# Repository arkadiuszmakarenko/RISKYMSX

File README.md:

# RISKYMSX

The RISKYMSX cartridge by Arkadiusz Makarenko is a compact MSX flash ROM cartridge based on the inexpensive CH32V30xVCT6 RISC-V MCU which can be easily programmed from a MSX computer using a FAT formatted USB pen drive containing ROM files.

## Main Features

* Support for up to 256KB ROMs
* SCC emulation
* Nextor 3.0 USB disk support for MSX-DOS programs and files
* Firmware programming with a WCH-LinkE; an experimental custom bootloader can update firmware from a USB stick
* ROM Flashing:
  * No external flash programmer is needed
  * A ROM can be flashed in-system using a MSX computer and a FAT-formatted USB pen drive
  * `ROM Flashing Mode` is activated by pressing GRAPH key during MSX boot
  * Automatic flashing of ROMs from USB can be achieved via specially named ROM archives
  * Manually flashing of ROMs from USB is done using a simple interactive menu
  * Automatic mapper type detection from the ROM content when flashing manually (same heuristic as openMSX)
  * FAT long filenames are supported
* Supported mappers:
  * Standard 16KB ROMs
  * Standard 32KB ROMs
  * Standard 48KB /64KB ROMs
  * KONAMI without SCC
  * KONAMI with SCC (EN - SCC emulation enabled)
  * KONAMI with SCC (DIS - SCC emulation disabled)
  * ASCII 8K
  * ASCII 16K
  * Neo 8k
  * Neo 16k

## Hardware

The RISKYMSX cartridge is made up of a 4-layer PCB with a reduced set of SMD components and through-hole connectors:
* A WCH [CH32V303VCT6](https://www.wch-ic.com/products/CH32V303.html) MCU (or alternatively a [CH32V307VCT6](https://www.wch-ic.com/products/CH32V307.html))
* Two LEDs, one to indicate power on state, and one lit during `ROM Flashing Mode`
* On rev 2.2, a CH217K current-limited switch controls power to the USB host port
* A [LM1117](https://www.ti.com/lit/ds/symlink/lm1117.pdf) voltage regulator to provide +3V3 to the MCU from the +5V rail of the MSX cartridge slot
* A [MCP6001](https://ww1.microchip.com/downloads/aemDocuments/documents/MSLD/ProductDocuments/DataSheets/MCP6001-1R-1U-2-4-1-MHz-Low-Power-Op-Amp-DS20001733L.pdf) operational amplifier to enhance the SCC audio signal fed into the MSX cartridge SOUNDIN pin
* Three headers:
  * B0: open for normal operation; closed to select system boot, including the optional custom bootloader
  * DAT/CLK: unconnected by default, used to program the MCU using the [`WCH-LinkE`](https://www.wch-ic.com/products/WCH-Link.html) programmer via SWDIO/SWCLK
  * RX/TX: unconnected by default, serial debug console
* One USB Type-A female connector
* Several passives required for proper operation of the above components

### Revisions

There are several hardware revisions of the cartridge. The main ones are listed here in reverse chronological order.

#### Rev 2.2 (current)

Rev 2.2 adds a CH217K switch to the USB host port. Its active-low enable is
controlled by PB12 and its fault output is connected to PB13. The USB port is
intended to power a USB drive, not to power the cartridge from a PC. Use
firmware that supports this switch.

The [schematic and PCB](board/), [rev 2.2 Gerbers](board/gerbers/RISKYMSXv22.zip),
and [schematic BOM](RISKYMSXCart.csv) are in this repository. The BOM requires
verification before ordering or assembly.

#### Rev 2.1 (older)

This version introduces the following changes:
* the flash button is removed, as the flashing interface can be accessed by pressing the GRAPH key on the MSX keyboard during boot
* unnecessary leds are removed, leaving just the Flash and Power leds
* the audio amplifier circuit is enhanced with a low pass filter 

#### Rev 2 (obsolete)

This version introduces the following changes:
* the LM1117 voltage regulator and related passives are moved to the back of the PCB
* the B1 header is removed as it has no practical use
* a simple audio amplifier circuit is added for SCC sound

|
|-|-|
|RISKYMSX Rev 2 front render|RISKYMSX Rev 2 rear render|

#### Rev 1 (obsolete)

This is the initial revision of the RISKYMSX cartridge.

|
|-|-|
|RISKYMSX Rev 1 front render|RISKYMSX Rev 1 rear render|

## Firmware

The firmware implements two different modes of operation for the RISKYMSX cartridge:
* `Normal Mode`. In this mode a ROM cartridge is emulated according to the last ROM flashed using the `ROM Flashing Mode`.
* `ROM Flashing Mode`. In this mode a ROM can be flashed manually or automatically into the cartridge by using a FAT formatted USB pen drive.

### Automated releases

GitHub Actions builds the bootloader, firmware, and Nextor cartridge on pushes
and pull requests to `main`. Pushing a version tag matching
`firmware/User/version.h` (currently `v4.2.1`) automatically creates a GitHub
Release containing:

* Firmware `.bin` and `.hex` files, plus the `CART.NXT` Nextor cartridge image
* `Bootloader.bin`, the experimental custom bootloader image (not application firmware)
* A ZIP of the PCB Gerber and drill files
* `SHA256SUMS` checksums for the release files

Successful pushes to `main` also update the `latest-build` prerelease with
the same assets and the commit SHA, if the built commit is still the tip of
`main`. Its tag and assets are replaced on each update; older rolling builds
are not retained. If the current build fails, the previous release remains.
Versioned releases remain separate, and pull requests do not publish releases.

The BOM is not included in new release packages. Previously published releases
may contain an outdated BOM. Verify the current schematic BOM before ordering
parts.

Create and push a tag to publish a release:

```bash
git tag v4.2.1
git push origin v4.2.1
```

## Building a RISKYMSX cartridge

You will need good soldering skills and specific equipment to build a RISKYMSX cartridge.
As you probably saw on the Bill Of Materials, there are quite small SMD components like 0603 passives and a LQFP-100 package with 0.5mm pitch that need to be soldered.

> [!WARNING]
> If you are building new boards, please use the current available board revision.

### PCB

The PCB can be fabricated from the [rev 2.2 Gerber archive](board/gerbers/RISKYMSXv22.zip).
The [rev 2.1 archive](RiskyMSXv21PCB.zip) is retained for older boards.

### Suggested tools

These are example tools used during the manual building of the RISKYMSX cartridge:

* silicone heat-resistant mat (TE-616 400x290mm), to avoid burning your precious desk
* electronic microscope with 2 LEDs (KKmoon 3" LCD 10X-300X 3.0MP 1080P HDMI electronic digital video microscope), to be able to solder those small 0.5mm pitch pins
* temperature controlled soldering station (Yihua 908D), to make good soldering joints
* T-1C "horseshoe", T-I and T-1.6D soldering tips (900M series), use the best fitting one for each soldering job
* copper sponge, for soldering head cleaning
* flux (Mechanic UV80 flux paste), to help keep components in place and achieve good soldering joints
* solder (0.5mm, for hobby projects you may use 60% Sn / 40% Pb Flux 2% at your own risk)
* desoldering wick (2.5mm is fine), for correcting mistakes if you are human)

### Components and assembly

The [CSV BOM](RISKYMSXCart.csv) is generated from the current schematic, but
is not a verified shopping list or assembly guide. Check component values,
ratings, footprints, orientation, and population before ordering or assembly.
U2 is `CH32V303VCT6`; the schematic retains the existing CH32V307 library
symbol, so verify its pin assignments against the CH32V303 datasheet.
The [interactive BOM](board/bom/ibom.html) shows the current PCB and its
component positions. It is also not a verified shopping list.

To regenerate the CSV with KiCad 10 from the repository root:

```sh
kicad-cli sch export bom \
  --fields 'Reference,Value,Footprint,QUANTITY,DNP' \
  --labels 'Reference,Value,Footprint,Qty,DNP' \
  --group-by 'Value,Footprint,DNP' --ref-range-delimiter '' \
  -o RISKYMSXCart.csv board/RISKYMSXCart.kicad_sch
```

The `DNP` column records KiCad's do-not-populate status. The list includes the
MSX edge connector footprint, which is part of the PCB rather than a separate
component. KiCad's PCB DRC reports footprint-library warnings; review those
before fabrication.

To regenerate the interactive BOM, install the KiCad 10-compatible
[InteractiveHtmlBom](https://github.com/openscopeproject/InteractiveHtmlBom)
plugin and run it from PCB Editor, or use its command-line tool:

```sh
generate_interactive_bom --no-browser --dest-dir bom board/RISKYMSXCart.kicad_pcb
```

The interactive BOM is generated from PCB values; synchronize the PCB with the
schematic and check for mismatches before regenerating it.

### Building the firmware on Linux

> [!NOTE]
> These instructions have been validated using Ubuntu 24.04.2 LTS.

#### Cloning the RISKYMSX github repository

```bash
cd $HOME
git clone 'https://github.com/arkadiuszmakarenko/RISKYMSX.git'
```

This will clone the RISKYMSX github repository to the `RISKYMSX` directory under your home directory.

#### Installing the [MounRiverStudio IDE](http://www.mounriver.com)

1. Download the MounRiverStudio package for Linux

[http://www.mounriver.com/download](http://www.mounriver.com/download)

Choose the package in `tar.xz` format.

2. Uncompress the MounRiverStudio package into a known directory

For example this will uncompress the MounRiverStudio package into the IDE directory under your home directory.

```bash
export IDEDIR=$HOME/IDE
mkdir -p $IDEDIR && cd $IDEDIR
tar xJvf /path/to/MounRiverStudio_Linux_X64_V210.tar.xz
```

Once uncompressed, all package files are under the `MRS2` directory.

3. Setup the MounRiverStudio

You can follow the instructions described on the `README` file.
Alternatively, if you don't want to install library files system-wide you can follow these instructions:

* Change to the `MRS2/beforeinstall` directory

```bash
cd MRS2/beforeinstall
```

* Make a backup of the `start.sh` script file for reference

```bash
cp start.sh start.sh.orig
```

* Modify the `start.sh` script file.

Comment out the lines that install libraries and the line that gives world write access to all files under the `MRS-linux-x64` directory.
Leave as is the code that copies the udev rules for the WCH programmers and reloads them into udevadm.

```bash
#! /bin/bash
#echo  -e "\nCopy Libs"
#sudo cp -P ./lib*    /usr/lib
#echo  -e "Register new Libs"
#sudo ldconfig
echo "copy rules"
sudo cp ./50-wch.rules /etc/udev/rules.d
sudo cp ./60-openocd.rules  /etc/udev/rules.d
echo "Reload rules"
sudo udevadm control  --reload-rules

#chmod -R 777 ../MRS-linux-x64
chmod -R 750 ../MRS-linux-x64

echo -e "DONE"
```

* Run the modified `start.sh` script

```bash
chmod u+x start.sh
./start.sh
```

* Make the `chrome-sandbox` executable suid to root by changing the ownership of the file to root and setting the SUID bit.

This is required as the MounRiverStudio IDE is an Electron-based application that uses a sandbox approach.

```bash
cd ../MRS-linux-x64
sudo chown root chrome-sandbox
sudo chmod 4755 chrome-sandbox
```

#### Launching the MounRiverStudio IDE

If you installed the MounRiverStudio IDE under `$HOME/IDE`, use the following complete command line whenever you need to launch MounRiverStudio IDE specifying where to find the extra libraries needed.

```bash
cd $HOME/IDE/MRS2/MRS-linux-x64
LD_LIBRARY_PATH=$(readlink -f ../beforeinstall/) ./mounriver-studio\ 2
```

#### Generating the firmware file

1. After launching the MounRiverStudio IDE, open the RISKYMSXCART project file

`File | Open MounRiver Project`

**`/path/to/your/RISKYMSX/firmware/RISKYMSXCART.wvproj`**

The project file is under the `firmware` directory on the cloned github repository.

2. Build the project

`Project | Build Project`

#### Generating the firmware file from the command line

As an alternative to the MounRiverStudio IDE, the firmware can be built and flashed directly from the command line using GNU `make`.

Requirements:

* GNU `make`
* A RISC-V toolchain. The Makefile auto-detects, in order:
  1. A locally installed `MRS_Toolchain_Linux_x64_V210/RISC-V Embedded GCC12` at the repository root (not shipped in the repo)
  2. `riscv-wch-elf-gcc` on `PATH` (the same compiler MounRiver uses)
  3. `riscv-none-embed-gcc` on `PATH` (xPack)
  4. `riscv64-unknown-elf-gcc` on `PATH` (system package)
* For `make flash`: OpenOCD with WCH-Link support (the Makefile uses the WCH version from the local MounRiver toolchain when available)
* For rebuilding `CART.NXT`: the .NET runtime needed by the vendored N80 assembler

The default build also attempts to build Nextor and copy it to `build/CART.NXT`.
It prints a warning rather than failing if the Nextor build fails; check the
output and do not assume an existing `CART.NXT` is fresh.

#### Building all images from the repository root

Run `make` from the repository root to build the bootloader, firmware, and
Nextor cartridge. The output files are placed in the root:
`Bootloader.bin`, `RISKYMSXCART.bin`, `RISKYMSXCART.hex`, and `CART.NXT`.
Individual builds are available with `make bootloader`, `make firmware`, or
`make nextor`; `make clean` removes the local firmware and bootloader outputs
and build directories. It leaves the tracked `CART.NXT` release image in place.

Build the firmware:

```bash
cd firmware
make            # produces build/RISKYMSXCART.{elf,bin,hex,map}
make size       # show program/data sizes
make clean      # remove build artifacts
```

Build and program the chip with OpenOCD and a WCH-LinkE:

```bash
make flash
```

You can override the toolchain explicitly, for example to force a clean build with the xPack toolchain:

```bash
make TOOLCHAIN_DIR=/opt/xpack PREFIX=riscv-none-embed- clean all
```

#### Programming the firmware

Firmware programming changes the MCU application, whereas ROM flashing in the
cartridge menu only selects an MSX ROM. Use a WCH-LinkE for initial programming
and recovery. The optional custom bootloader offers a different, experimental
way to update the application from an MSX and USB stick after installation.

> [!WARNING]
> On rev 2.2 the CH217K switches the USB host VBUS. A USB cable connected to
> a PC is not a suitable source of cartridge power. The old USB ISP
> cable-only instructions do not apply to this revision. USB ISP with an
> independently powered board has not been validated here.
>
> Use a properly powered target and a common ground with the WCH-Link. A
> specific standalone power connection for rev 2.2 has not yet been
> validated; consult the schematic and verify the supply, voltage and
> connections before programming. Do not bypass the switch or connect
> multiple power sources based on the old instructions.

##### Programming the application with WCH-LinkE

1. With power off, connect WCH-LinkE SWCLK/TCK to J8 CLK, SWDIO/TMS to
   J8 DAT, and the programmer ground to target ground. Follow the
   [WCH-Link manual](https://www.wch-ic.com/downloads/WCH-LinkUserManual_PDF.html)
   for the programmer's target-voltage requirements and RISC-V mode.
2. Provide the target with a verified supply, connect the WCH-LinkE to the PC
   and confirm the cartridge is powered. The target power arrangement must be
   verified for the board revision; it is not supplied by the USB host port.
3. Use `make flash` in `firmware/`, or select the built
   `firmware/obj/RISKYMSXCART.hex` in MounRiverStudio under
   `Flash | Download Configuration` and use `Flash | Download`. The
   command-line build produces `firmware/build/RISKYMSXCART.hex` instead.
4. Verify the operation with the programmer. Power down before disconnecting
   wires or inserting or removing the cartridge. Keep B0 open for normal boot.

##### Updating with the custom bootloader (experimental)

The [custom bootloader](bootloader/README.md) is not the CH32V303 factory ISP
bootloader. It occupies the 28 KiB system boot flash and must first be
installed using a WCH-Link and a compatible `minichlink`; it is not installed
by programming the normal application firmware.

> [!CAUTION]
> Replacing the factory bootloader is untested and hardware-dependent. It
> removes factory USB/USART ISP while installed, and a failed write or unusable
> backup can prevent recovery. Back up the system boot region first, keep the
> WCH-Link available, and read the complete
> [installation and recovery instructions](bootloader/README.md) before
> proceeding. Flash programming and MSX bus timing need hardware validation.

After the custom bootloader has been installed and validated:

1. Copy the application binary to the root of a FAT-formatted USB stick as
   `RISKYMSXCART.BIN`. The bootloader also checks `FIRMWARE.BIN` and
   `UPDATE.BIN`, in that order. Release binaries with a version in their name
   must be renamed.
2. With the MSX powered off, close B0, insert the cartridge and USB stick, and
   power on the MSX. B0 selects system boot; the cartridge is powered by the
   MSX, not by the USB stick.
3. Follow the MSX screen: press Return to program or Esc to cancel. Wait for
   programming and read-back verification to finish.
4. Power off the MSX, open B0, then power on again to run the application.
   Never remove or insert the cartridge while the MSX is powered on.

## Cartridge Operation

The RISKYMSX cartridge can operate in two different modes once programmed with the RISKYMSX firmware.

Make sure the MSX computer is powered off before inserting or removing the RISKYMSX cartridge or any other cartridge.

> [!WARNING]
> Leave DAT/CLK and RX/TX unconnected for ordinary cartridge operation. B0
> must be open for normal boot; closing it selects system boot for the
> optional custom bootloader.

### Normal Mode

In `Normal mode` the RISKYMSX cartridge behaves as a ROM cartridge once a ROM has been flashed.

Just insert the RISKYMSX cartridge and enjoy the already flashed ROM.

### ROM Flashing Mode

In `ROM Flashing Mode` a ROM file residing in a USB drive can be flashed to the RISKYMSX cartridge for later use in `Normal Mode`.

1. Make sure the MSX computer is powered off

2. Insert the RISKYMSX cartridge

3. Press and hold the `GRAPH` key on the MSX computer keyboard and power on the MSX computer.

You can release the `GRAPH` key once you see the Flash LED turn on.

4. If no USB drive is connected to the RISKYMSX cartridge, the "Insert USB" screen will appear.

You will need to connect a FAT-formatted USB drive to continue the ROM flashing procedure.

Once that is done, the RISKYMSX will try first to auto-flash a ROM before switching to manually flashing ROMs.

#### Auto-flashing ROMs

The RISKYMSX firmware will automatically flash the first file found on the root directory of the connected FAT-formatted USB drive matching one of the special filenames for ROM auto-flashing, according to the following table. A mapper will be automatically assigned based on the filename detected.

 | Mapper               | filename         | 
 |   :-----------:      | :--------------: | 
 | 16KB ROM             | cart.r16         | 
 | 32KB ROM             | cart.r32         | 
 | 48KB / 64KB ROM      | cart.r48         |
 | KONAMI without SCC   | cart.ko4         |
 | KONAMI with SCC(EN)  | cart.ko5         |
 | KONAMI with SCC(DIS) | cart.kd5         |
 | ASCII8k              | cart.a8k         | 
 | ASCII16k             | cart.a16         | 
 | NEO16                | cart.n16         | 
 | NEO8                 | cart.n8k         | 

So for example, to automatically flash F1SPIRIT.ROM, which is a KONAMI with SCC game, the F1SPIRIT.ROM file can be copied to the root of the USB drive using the filename **cart.ko5**, and then follow the mentioned procedure.

After flashing the ROM file, the RISKYMSX will automatically reboot the MSX computer and the ROM will load.

Note that if several files matching the auto-flashing filenames are found on the USB drive, only the file that causes the first match in the above table order will be flashed.

#### Manually flashing ROMs

If the connected FAT-formatted USB drive contains no files matching the auto-flashing filenames, the RISKYMSX firmware will display the interactive ROM flashing menu.

Use the following keys to interact with the file menu screen:
* `Up`, `Down`: move up or down the red arrow cursor across the available files in the current page
* `Right`: go to the next page (if more files are available to list)
* `Left`: go to the previous page (if any pagination was done before)
* `Return`: select a file for flashing
* `Esc`: go to the previous screen, or reload the file list on the root directory
* `1`: show the current flashed ROM file and mapper type, and optionally change the mapper type
* `N`: flash `CART.NXT` from the USB root as a Nextor cartridge
* `Backspace`: go to the previous directory level on the file menu

Useful tips:
* The bottom of the file menu screen shows the keys that are available to use at any moment
* Files and directories are listed alphabetically (directories first, upper/lowercase ignored), regardless of how many files a folder contains
* You can always hot-swap the USB drive while in the file menu, and once a new USB drive is connected you need to press `Esc` to refresh the file contents
* DO NOT navigate or select files while you have disconnected a USB drive without pressing `Esc` first
* Pressing `1` and choosing `SCC only (no ROM)` stores only the mapper setting in the config area (no ROM data is flashed). The cart then emulates just the SCC (0x9000-0x98FF, triggered by CS2 rather than SLTSL) on every boot unless GRAPH is held to enter the terminal
* If you flash a ROM with the wrong mapper type, you can change the mapper type easily, without reflashing the ROM again, by pressing `1` (the mapper type detected from the flashed ROM content is pre-selected there too)

When a ROM file is selected by pressing the `Return` key the mapper selection screen shows up. The mapper type is auto-detected from the ROM content and pre-selected (shown as `Detected:`), so pressing `Return` again flashes the ROM with the detected mapper. You can still move the cursor to pick a different mapper type before pressing `Return`.

Select the correct mapper type for the selected ROM file and press `Return` to start flashing the ROM.

Once the flashing process finishes the RISKYMSX firmware will reboot the MSX computer and the flashed ROM will load.

#### Nextor USB disk

Nextor 3 turns the cartridge into a USB mass-storage disk controller for
MSX-DOS. The cartridge exposes one USB device to Nextor, which maps its
compatible partitions to MSX drives.

**Minimum for the Nextor 3 DOS environment:**

* An MSX with at least 128 KiB of mapped RAM, a RISKYMSX cartridge with the
  current firmware, and the Nextor cartridge image `CART.NXT`.
* A USB mass-storage device with 512-byte sectors, an MBR partition table
  (not GPT), and a FAT16 or FAT12 partition. FAT16 is recommended. Nextor
  does **not** support FAT32, exFAT, or NTFS.
* Stable Nextor 3.0 `NEXTOR.SYS` and `COMMAND3.COM` in the root of the
  partition used to boot.

Without 128 KiB of mapped RAM, Nextor falls back to MSX-DOS 1 mode; that
mode requires a FAT12 partition with at most three sectors per FAT and, for
the DOS prompt, at least 64 KiB of RAM plus the MSX-DOS 1 system files. See the
[Nextor user manual](https://konamiman.github.io/Nextor/Nextor_3.0_User_Manual.html)
for details.

**Enable and boot Nextor:**

1. Get `CART.NXT` from a [RISKYMSX release](https://github.com/arkadiuszmakarenko/RISKYMSX/releases)
   or run `make nextor` at the repository root.
2. Copy `CART.NXT` to the root of a FAT-formatted USB stick for flashing.
   Enter ROM flashing mode by holding `GRAPH` at startup, and press `N` in
   the file menu. This replaces the currently flashed cartridge ROM with
   Nextor; it does not replace the MCU firmware.
3. Prepare a separate Nextor USB disk as described above. Download
   [Nextor 3.0 tools.zip](https://github.com/Konamiman/Nextor/releases/tag/tools-disk-image-and-zip-for-Nextor-3.0),
   extract it, and copy `NEXTOR.SYS` and `COMMAND3.COM` to the boot
   partition's root. The `TOOLS` and `HELP` directories are optional but
   useful; copy them as well if desired.
4. Insert the Nextor disk and restart the MSX normally, without holding
   `GRAPH`. The flashed Nextor kernel loads the system files from the disk.

Nextor maps active FAT12/16 partitions at boot; if none is active, it uses the
first suitable partition. Partitioning or formatting erases data, so back up
the USB device first. For partitioning and other commands, see the
[Nextor getting started guide](https://konamiman.github.io/Nextor/Nextor_3.0_Getting_Started_Guide.html)
and [Nextor downloads](https://konamiman.github.io/Nextor/releases/). The
kernel and system files must be compatible; this build uses stable Nextor 3.0
([Nextor build](NextorDriver/Makefile)).

## General troubleshooting

* If no LEDs light at power-up, check the power rails and inspect for shorts.
* On rev 2.2, a rapidly flashing activity LED can indicate a CH217K
  over-current or over-temperature fault. The firmware disables USB power and
  latches the fault until reset. Remove the cause before resetting.
* If a ROM can be programmed but the MSX cannot load it, inspect the address,
  data and bus connections and their solder joints.

## Compatibility

The RISKYMSX cartridge has been tested on the following MSX computers:

| **Model**                | **RISKYMSX**              |
|--------------------------|---------------------------|
| Sony MSX HB-101P         |          OK               |
| Sony MSX HB-501F         |          OK               |
| Toshiba MSX HX-10        |          OK               |
| Philips MSX2 VG-8235     |          OK               |
| Panasonic MSX2+ FS-A1WSX |          OK               |
| Omega MSX2+              |          OK               |
| Tides Rider MSX2+        |          OK               |
| TFMSX Rev 1 MSX2+        |          OK               |
| TFMSX Rev 2 MSX2+        |          OK               |
| MSXVR                    |          `NOK`            |

Other MSX compatible computers will probably work too, but have not been specifically tested.

## Enclosures

### Acrylic Enclosure

You can complete your RISKYMSX cartridge with an [acrylic enclosure](https://github.com/herraa1/msx-riskymsx-enclosure) suitable for all RISKYMSX cartridge board revisions.

### 3D Printed Enclosure

Another option for closing your RISKY MSX Cartridge is following project  [Enclosure](https://github.com/rafaelan00/RISKYMSX-Enclosure)

## Acknowledgments

The following people contributed to this project and supported me with technical aspects of this project.
* Terrible Fire
* cnlohr 
* NYYRIKKI
* Aoineko
* BG Ollie
* MadHacker

Testing team:
* PhilC
* Higgy
* ahmsx
* Hee-Bong An
  
Thank you very much for your support.

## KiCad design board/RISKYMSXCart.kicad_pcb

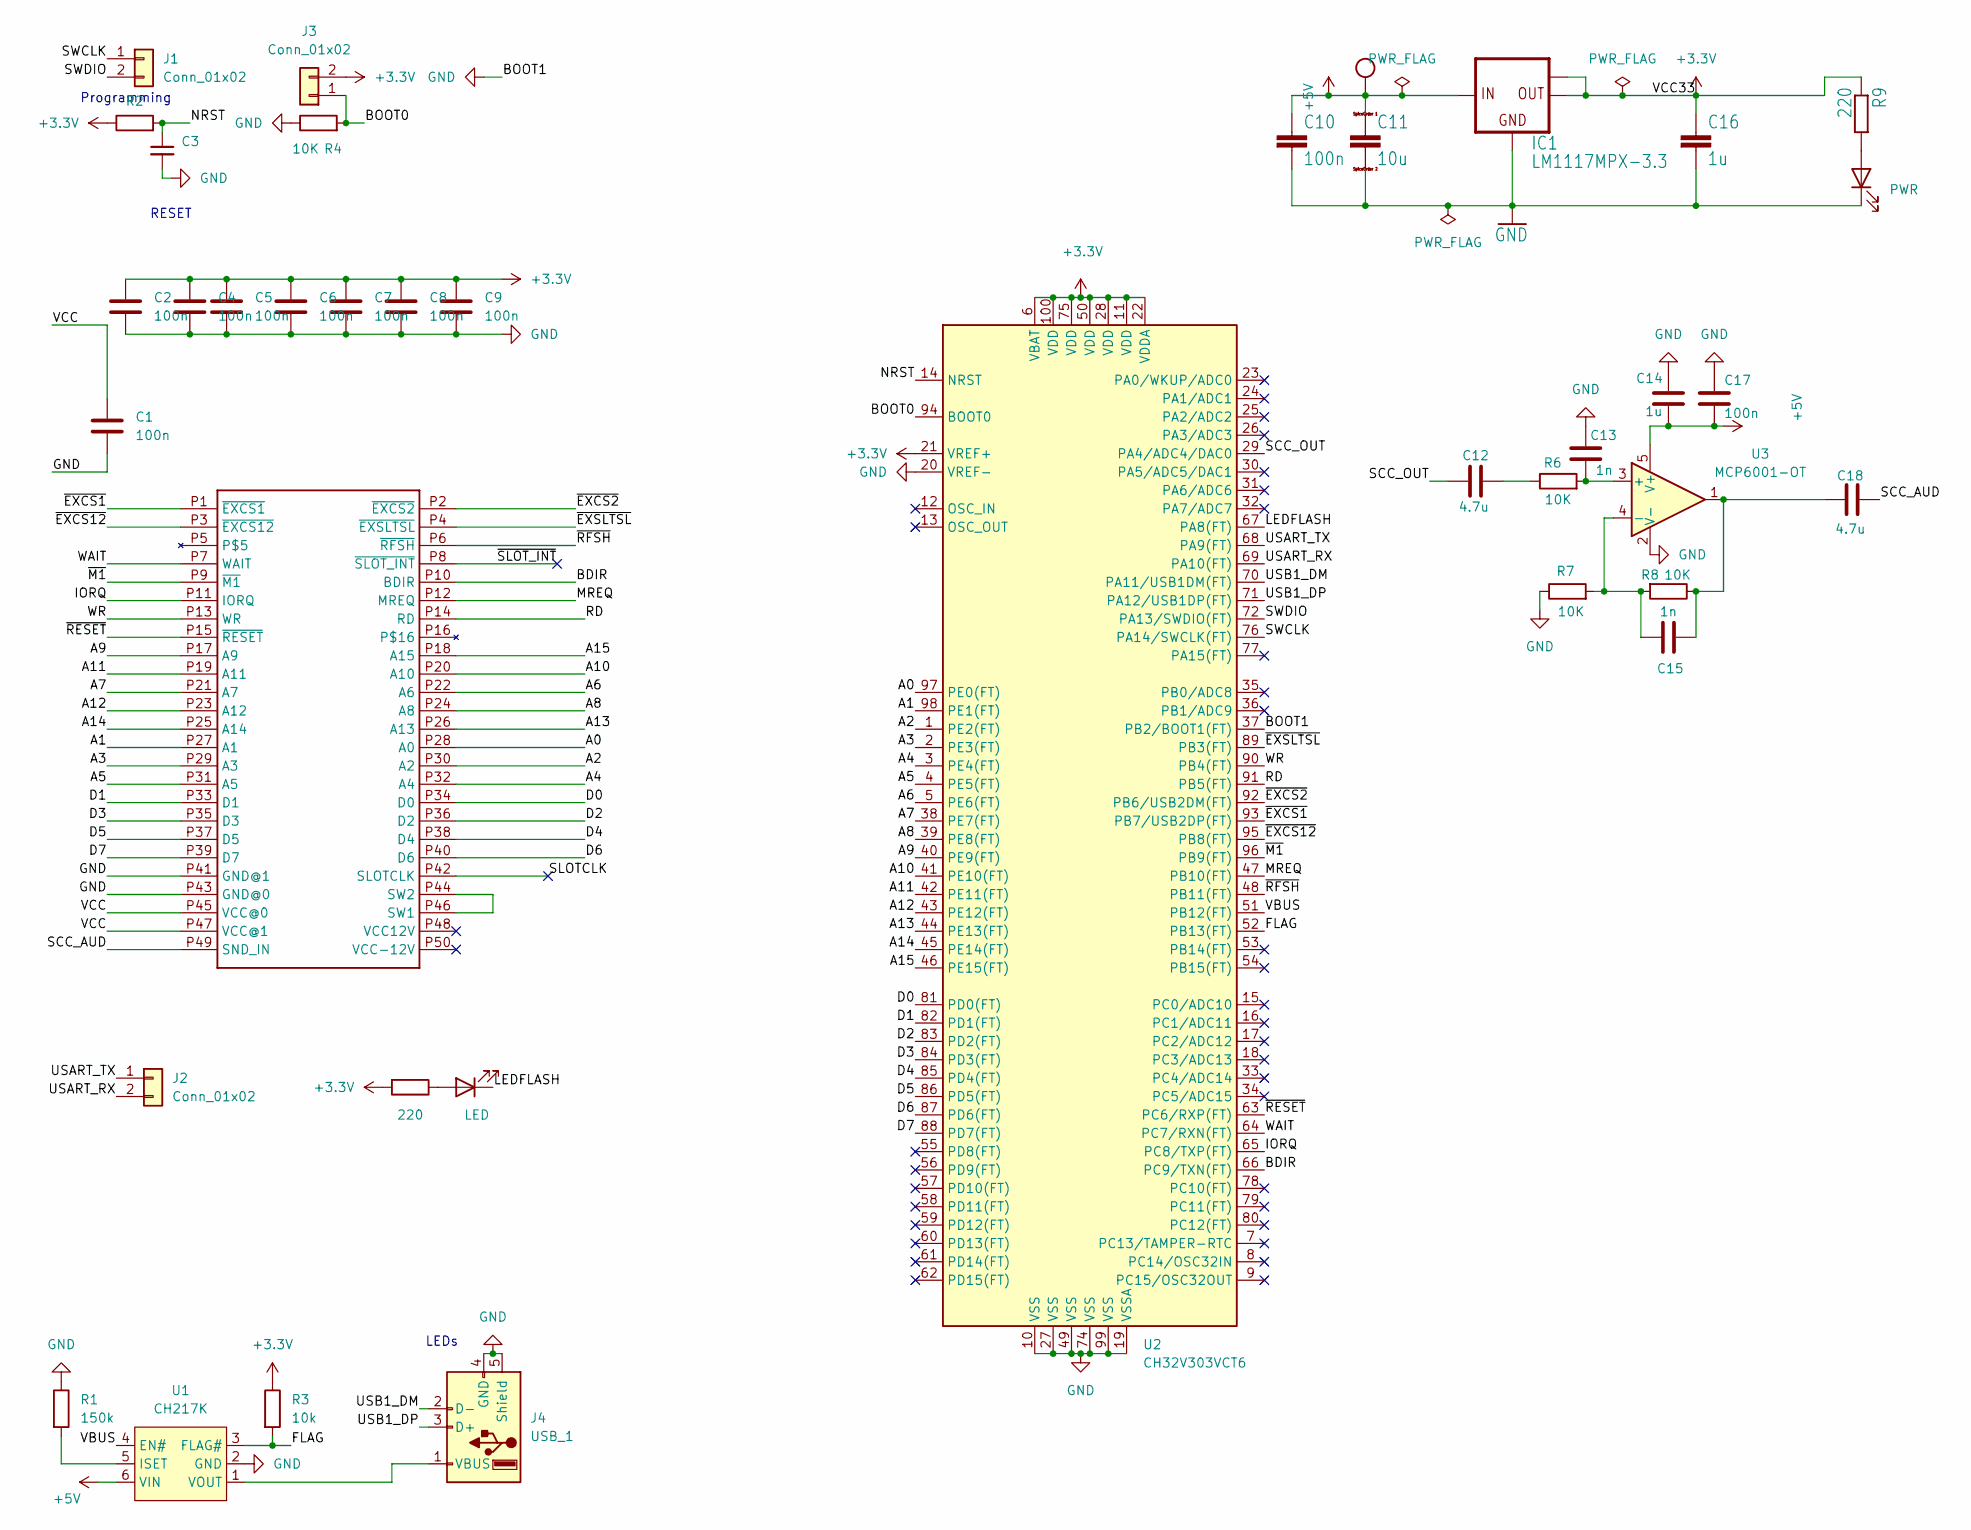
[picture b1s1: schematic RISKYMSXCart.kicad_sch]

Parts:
C1: 100n; C_1206_3216Metric_Pad1.33x1.80mm_HandSolder
C2, C4, C5, C6, C7, C8, C9, C17: 100n; C_0603_1608Metric_Pad1.08x0.95mm_HandSolder
C3: 100n; C_0603_1608Metric_Pad1.08x0.95mm_HandSolder; LCSC C14663
C10: 100n; C1206
C11: 10u; C0603
C12, C18: 4.7u; C_0603_1608Metric_Pad1.08x0.95mm_HandSolder
C13, C15: 1n; C_0603_1608Metric_Pad1.08x0.95mm_HandSolder
C14: 1u; C_0603_1608Metric_Pad1.08x0.95mm_HandSolder
C16: 1u; C1206
CN1: MSX_CART
D1: LED; LED_0805_2012Metric_Pad1.15x1.40mm_HandSolder
D2: PWR; LED_0805_2012Metric_Pad1.15x1.40mm_HandSolder
IC1: LM1117MPX-3.3; SOT223
J1, J2, J3: Conn_01x02; PinHeader_1x02_P2.54mm_Vertical
J4: USB_1; USB_A_CONNFLY_DS1095-WNR0
R1: 150k; R_0603_1608Metric_Pad0.98x0.95mm_HandSolder
R2, R4, R6, R7, R8: 10K; R_0603_1608Metric_Pad0.98x0.95mm_HandSolder
R3: 10k; R_0603_1608Metric_Pad0.98x0.95mm_HandSolder
R5: 220; R_0603_1608Metric_Pad0.98x0.95mm_HandSolder
R9: 220; R0603
U1: CH217K; SOT-23-6
U2: CH32V303VCT6; LQFP-100_14x14mm_P0.5mm
U3: MCP6001-OT; SOT-23-5

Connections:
+3.3V: C2.1, C4.1, C5.1, C6.1, C7.1, C8.1, C9.1, C16.1, IC1.2 (OUT), IC1.TAB (OUT1), J3.2, R2.1, R3.1, R5.2, R9.1, U2.6 (VBAT), U2.11 (VDD), U2.21 (VREF+), U2.22 (VDDA), U2.28 (VDD), U2.50 (VDD), U2.75 (VDD), U2.100 (VDD)
+5V: C1.1, C10.1, C11.1, C14.2, C17.2, CN1.P45 (VCC@0), CN1.P47 (VCC@1), IC1.3 (IN), U1.6 (VIN), U3.5 (V+)
/A0: CN1.P28 (A0), U2.97 (PE0(FT))
/A1: CN1.P27 (A1), U2.98 (PE1(FT))
/A2: CN1.P30 (A2), U2.1 (PE2(FT))
/A3: CN1.P29 (A3), U2.2 (PE3(FT))
/A4: CN1.P32 (A4), U2.3 (PE4(FT))
/A5: CN1.P31 (A5), U2.4 (PE5(FT))
/A6: CN1.P22 (A6), U2.5 (PE6(FT))
/A7: CN1.P21 (A7), U2.38 (PE7(FT))
/A8: CN1.P24 (A8), U2.39 (PE8(FT))
/A9: CN1.P17 (A9), U2.40 (PE9(FT))
/A10: CN1.P20 (A10), U2.41 (PE10(FT))
/A11: CN1.P19 (A11), U2.42 (PE11(FT))
/A12: CN1.P23 (A12), U2.43 (PE12(FT))
/A13: CN1.P26 (A13), U2.44 (PE13(FT))
/A14: CN1.P25 (A14), U2.45 (PE14(FT))
/A15: CN1.P18 (A15), U2.46 (PE15(FT))
/BDIR: CN1.P10 (BDIR), U2.66 (PC9/TXN(FT))
/BOOT0: J3.1, R4.2, U2.94 (BOOT0)
/D0: CN1.P34 (D0), U2.81 (PD0(FT))
/D1: CN1.P33 (D1), U2.82 (PD1(FT))
/D2: CN1.P36 (D2), U2.83 (PD2(FT))
/D3: CN1.P35 (D3), U2.84 (PD3(FT))
/D4: CN1.P38 (D4), U2.85 (PD4(FT))
/D5: CN1.P37 (D5), U2.86 (PD5(FT))
/D6: CN1.P40 (D6), U2.87 (PD6(FT))
/D7: CN1.P39 (D7), U2.88 (PD7(FT))
/FLAG: R3.2, U1.3 (FLAG#), U2.52 (PB13(FT))
/IORQ: CN1.P11 (IORQ), U2.65 (PC8/TXP(FT))
/LEDFLASH: D1.1 (K), U2.67 (PA8(FT))
/MREQ: CN1.P12 (MREQ), U2.47 (PB10(FT))
/NRST: C3.1, R2.2, U2.14 (NRST)
/RD: CN1.P14 (RD), U2.91 (PB5(FT))
/SCC_AUD: C18.2, CN1.P49 (SND_IN)
/SCC_OUT: C12.1, U2.29 (PA4/ADC4/DAC0)
/SLOTCLK: CN1.P42 (SLOTCLK)
/SWCLK: J1.1, U2.76 (PA14/SWCLK(FT))
/SWDIO: J1.2, U2.72 (PA13/SWDIO(FT))
/USART_RX: J2.2, U2.69 (PA10(FT))
/USART_TX: J2.1, U2.68 (PA9(FT))
/USB1_DM: J4.2 (D-), U2.70 (PA11/USB1DM(FT))
/USB1_DP: J4.3 (D+), U2.71 (PA12/USB1DP(FT))
/VBUS: U1.4 (EN#), U2.51 (PB12(FT))
/WAIT: CN1.P7 (WAIT), U2.64 (PC7/RXN(FT))
/WR: CN1.P13 (WR), U2.90 (PB4(FT))
/~EXCS1: CN1.P1 (~EXCS1), U2.93 (PB7/USB2DP(FT))
/~EXCS2: CN1.P2 (~EXCS2), U2.92 (PB6/USB2DM(FT))
/~EXCS12: CN1.P3 (~EXCS12), U2.95 (PB8(FT))
/~EXSLTSL: CN1.P4 (~EXSLTSL), U2.89 (PB3(FT))
/~M1: CN1.P9 (~M1), U2.96 (PB9(FT))
/~RESET: CN1.P15 (~RESET), U2.63 (PC6/RXP(FT))
/~RFSH: CN1.P6 (~RFSH), U2.48 (PB11(FT))
/~SLOT_INT: CN1.P8 (~SLOT_INT)
GND: C1.2, C2.2, C3.2, C4.2, C5.2, C6.2, C7.2, C8.2, C9.2, C10.2, C11.2, C13.2, C14.1, C16.2, C17.1, CN1.P41 (GND@1), CN1.P43 (GND@0), D2.1 (K), IC1.1 (GND), J4.4 (GND), J4.5 (Shield), R1.1, R4.1, R7.1, U1.2 (GND), U2.10 (VSS), U2.19 (VSSA), U2.20 (VREF-), U2.27 (VSS), U2.37 (PB2/BOOT1(FT)), U2.49 (VSS), U2.74 (VSS), U2.99 (VSS), U3.2 (V-)
unnamed: C12.2, R6.1
unnamed: C15.2, C18.1, R8.1, U3.1
unnamed: CN1.P44 (SW2), CN1.P46 (SW1)
unnamed: D1.2 (A), R5.1
unnamed: D2.2 (A), R9.2
unnamed: J4.1 (VBUS), U1.1 (VOUT)
unnamed: R1.2, U1.5 (ISET)
unnamed: C13.1, R6.2, U3.3 (+)
unnamed: C15.1, R7.2, R8.2, U3.4 (-)

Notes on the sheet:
RESET
Programming
LEDs

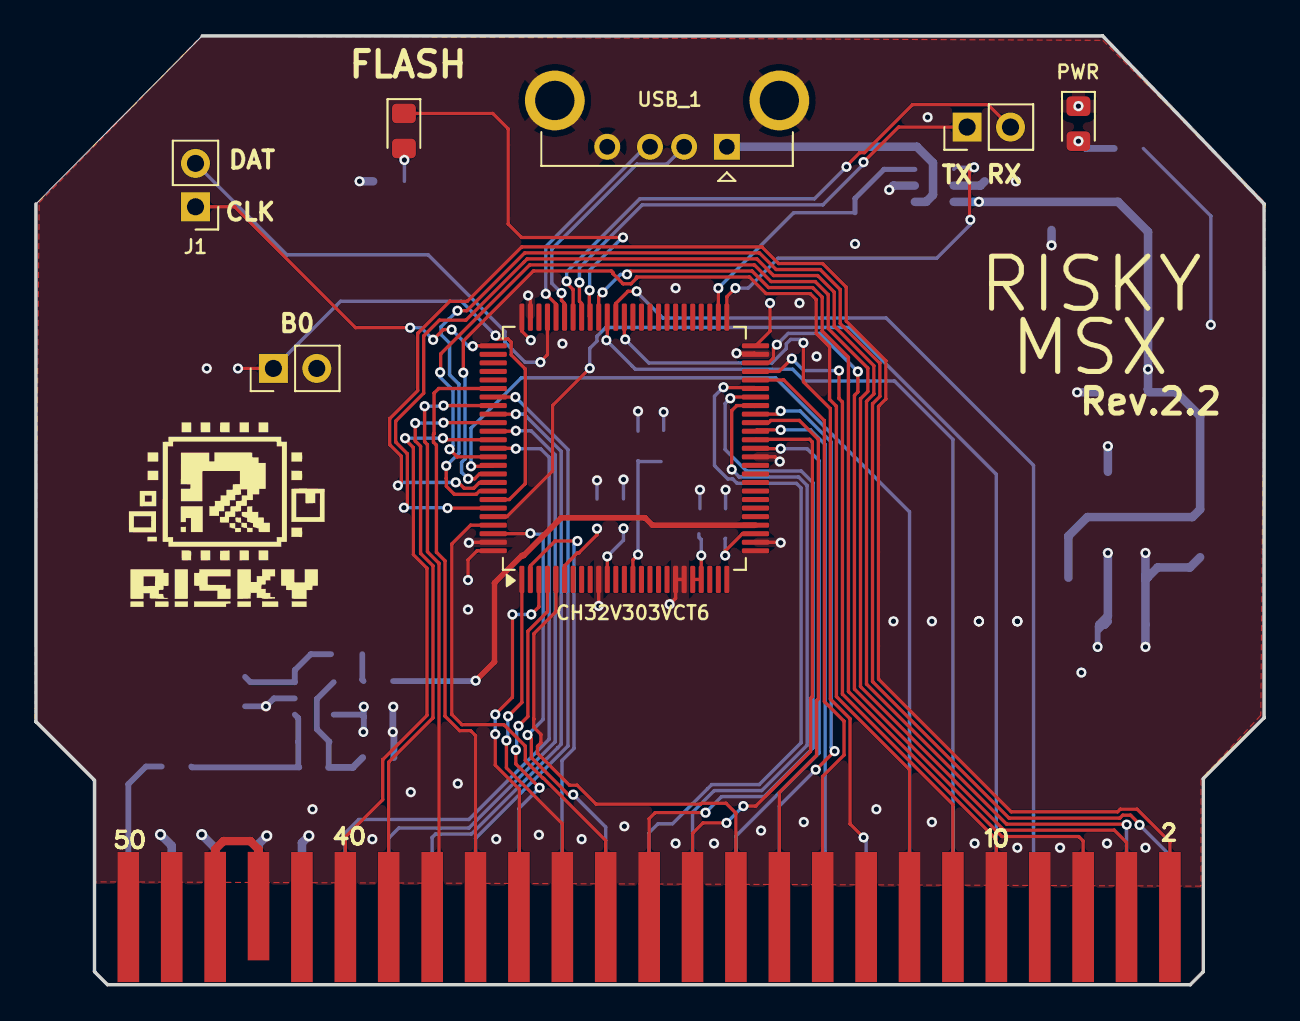
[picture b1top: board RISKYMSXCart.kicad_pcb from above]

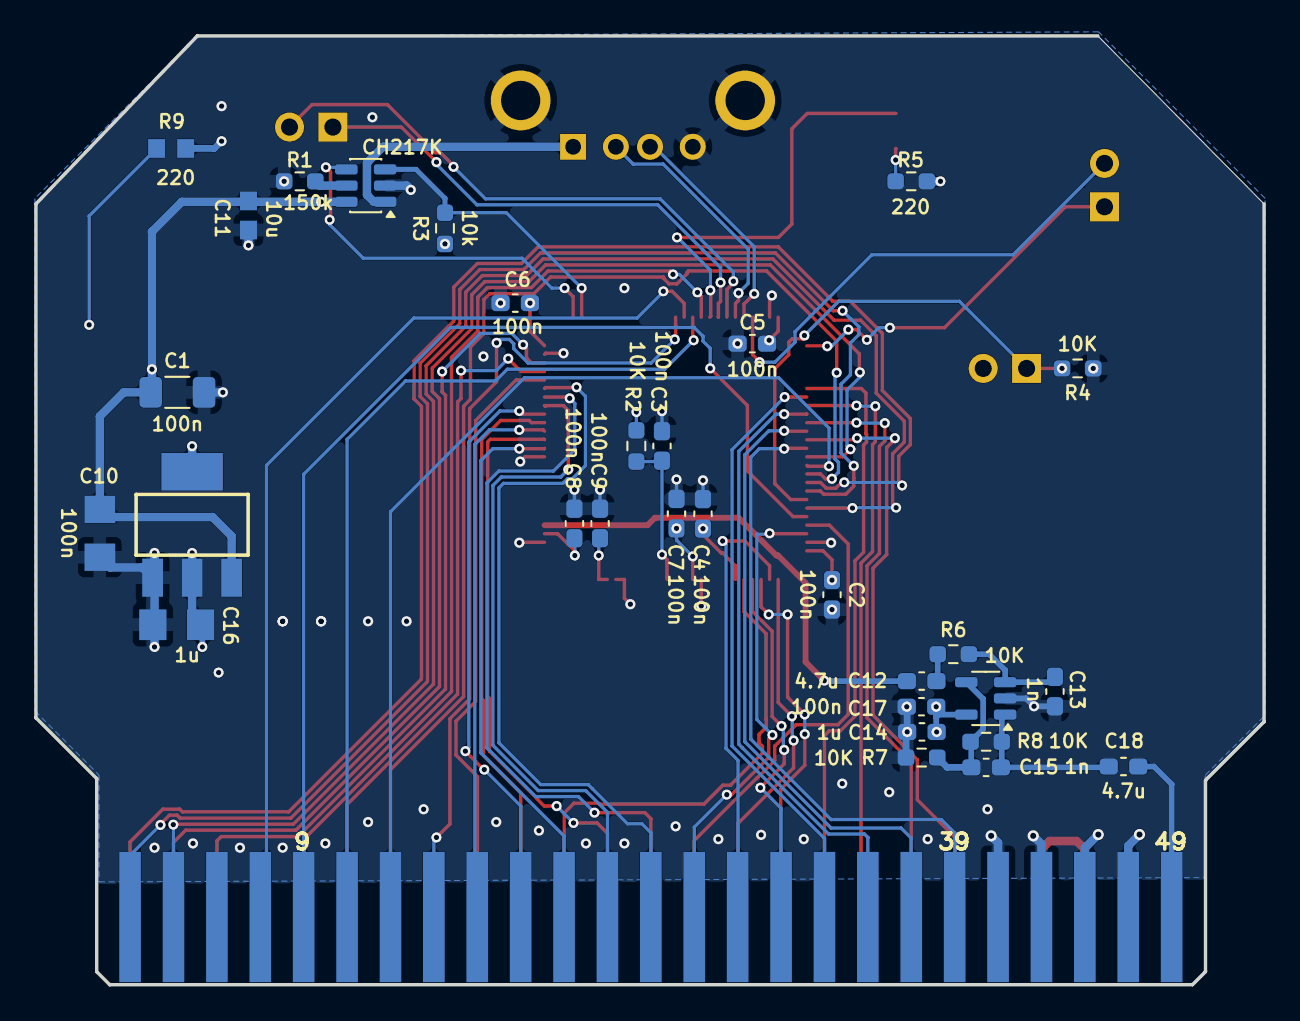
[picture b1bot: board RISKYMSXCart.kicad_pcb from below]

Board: 4 copper layers, 71.9 x 55.5 mm, 38 parts (30 on the bottom side), 62 nets.

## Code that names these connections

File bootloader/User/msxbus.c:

#include "msxbus.h"
#include "ch32v30x.h"
#include <string.h>

/*
 * MSX cartridge bus interception.
 *
 * GPIOE carries the address, GPIOD the data bus. PB3 is SLT, PB4 WR and PB5
 * RD, all active low. The MSX side program (MSXTerminal/msxterminal.asm)
 * reads a byte from #7FFF and writes a byte to #7FFD. #7FFE selects the
 * terminal (0) or the cartridge ROM (non-zero).
 */

MsxOutQueue msx_out;
MsxInQueue msx_in;
volatile uint8_t msx_terminal_requested;

/*
 * Handover flag for switching from the terminal to the cartridge ROM.
 *
 * The cartridge firmware reads this byte at startup: a non-zero value means
 * the terminal handed over to the ROM, a zero value means the terminal mode
 * was requested. The address is the same one the cartridge firmware uses, so
 * the two agree on the protocol across the reset.
 */
#define MSX_CART_RAM_FLAG ((volatile uint8_t *)0x20007C00u)

static const uint8_t msxterm[205] = {
    'A', 'B', '&', '@', 0x00, 0x00, 0x00, 0x00, 0x00, 0x00, 0x00, 0x00, 0x00, 0x00, 0x00, 0x00,
    'R', 'I', 'S', 'K', 'Y', '_', 'B', 'O', 'O', 'T', 0x00, '1', '.', '0', 0x00, 0x00, '>',
    0x04, '2', 0xfe, 0x7f, 0xc9, '!', '3', '@', 0x11, 0x00, 0xe0, 0x01, 0x92, 0x00, 0xd5, 0xed,
    0xb0, 0xc9, 0xaf, '2', 0xfe, 0x7f, '>', ' ', '2', 0xaf, 0xf3, '!', 0x0f, 0x00, '"', 0xea,
    0xf3, '"', 0xe9, 0xf3, '>', 0x01, 0xcd, '_', 0x00, '!', 0xc5, '@', 0x11, 0x00, '8', 0x01,
    0x08, 0x00, 0xcd, 0x5c, 0x00, '>', 0x08, '!', 0x03, 0x1b, 0xcd, 'M', 0x00, ':', 0xff, 0x7f,
    0xfe, 0x03, '(', '+', 0xfe, 0x04, '(', 0x14, 0xa7, 0xcc, 0x87, 0xe0, 0xc4, 0xa2, 0x00,
    0xcd, 0x9c, 0x00, '(', 0xe9, 0xcd, 0x9f, 0x00, '2', 0xfd, 0x7f, 0x18, 0xe1, ':', 0xff,
    0x7f, '!', 0x01, 0x1b, 0xcd, 'M', 0x00, ':', 0xff, 0x7f, '=', '-', 0xcd, 'M', 0x00, 0x18,
    0xce, 0xcd, 0x87, 0xe0, 0xcd, 0x87, 0xe0, '*', 0xb1, 0xf6, 0x11, 0xf4, 0xff, 0x19, 0xe5,
    '^', '#', 'V', '!', 0xa3, '}', 0xe7, 0xe1, ' ', 0x0c, 0x11, '|', 0xe0, 's', '#', 'r', 0xc9,
    0xc1, 0xe1, 0xc3, 0x84, '}', 0x1e, 'R', 0xcd, 0xb1, 0xff, 0xc7, 0xf5, 0xfb, '!', 0x9e,
    0xfc, '~', 0xbe, '(', 0xfd, 0xf1, 0xc9, ' ', '0', '8', '<', '8', '0', ' ', 0x00
};

void MsxBus_Init(void)
{
    msx_out.head = 0;
    msx_out.tail = 0;
    msx_in.head = 0;
    msx_in.tail = 0;
    msx_terminal_requested = 0;

    /* Clear the handover flag: the application firmware must not see a stale
       value from an earlier boot. */
    *MSX_CART_RAM_FLAG = 0;

    RCC->APB2PCENR |= RCC_APB2Periph_GPIOA | RCC_APB2Periph_GPIOB |
                      RCC_APB2Periph_GPIOC | RCC_APB2Periph_GPIOD |
                      RCC_APB2Periph_GPIOE | RCC_APB2Periph_AFIO;

    /* Address (GPIOE) and data (GPIOD) lines are inputs; the bus is driven
       only while a read cycle is being serviced. */
    GPIOE->CFGLR = 0x44444444;
    GPIOD->CFGLR = MSX_BUS_OFF;

    GPIO_InitTypeDef gpio;
    gpio.GPIO_Pin = GPIO_Pin_8;
    gpio.GPIO_Mode = GPIO_Mode_Out_PP;
    gpio.GPIO_Speed = GPIO_Speed_50MHz;
    GPIO_Init(GPIOA, &gpio);

    EXTI_InitTypeDef exti = {0};
    GPIO_EXTILineConfig(GPIO_PortSourceGPIOB, GPIO_PinSource3);
    exti.EXTI_Line = EXTI_Line3;
    exti.EXTI_Mode = EXTI_Mode_Interrupt;
    exti.EXTI_Trigger = EXTI_Trigger_Falling;
    exti.EXTI_LineCmd = ENABLE;
    EXTI_Init(&exti);

    NVIC_EnableIRQ(EXTI3_IRQn);
    SetVTFIRQ((uint32_t)MsxBus_Service, EXTI3_IRQn, 0, ENABLE);
}

void MsxBus_QueueByte(uint8_t value)
{
    uint8_t next = (uint8_t)((msx_out.head + 1) & (MSX_OUT_SIZE - 1));
    /* Wait for the MSX side to drain the queue instead of dropping the byte.
       A dropped byte in the middle of an escape sequence leaves the terminal
       in a broken state, and a dropped newline makes the output run together
       on one line. The cartridge firmware blocks the same way. */
    while (next == msx_out.tail) {
    }
    msx_out.data[msx_out.head] = value;
    msx_out.head = next;
}

void MsxBus_QueueString(const char *text)
{
    while (*text) {
        MsxBus_QueueByte((uint8_t)*text++);
    }
}

void MsxBus_Flush(void)
{
    while (msx_out.head != msx_out.tail) {
    }
}

int MsxBus_TakeInput(uint8_t *value)
{
    if (msx_in.head == msx_in.tail) {
        return 0;
    }
    *value = msx_in.data[msx_in.tail];
    msx_in.tail = (uint8_t)((msx_in.tail + 1) & (MSX_IN_SIZE - 1));
    return 1;
}

/*
 * The cartridge firmware checks this flag at startup: a non-zero value means
 * the terminal handed over to the ROM. The bootloader clears it on start, so
 * the application firmware does not mistake a bootloader run for a terminal
 * request.
 */
int MsxBus_RomModeRequested(void)
{
    return *MSX_CART_RAM_FLAG != 0;
}

void Vbus_Init(void)
{
    GPIO_InitTypeDef gpio;

    RCC->APB2PCENR |= RCC_APB2Periph_GPIOB;

    /* PB12 drives the CH217K EN# input: push pull output, initially high so
       the port stays unpowered until it is explicitly enabled. */
    gpio.GPIO_Pin = GPIO_Pin_12;
    gpio.GPIO_Mode = GPIO_Mode_Out_PP;
    gpio.GPIO_Speed = GPIO_Speed_50MHz;
    GPIO_Init(GPIOB, &gpio);
    GPIO_SetBits(GPIOB, GPIO_Pin_12);

    /* PB13 reads the CH217K FLAG# output: active low, open drain, held high
       by an internal pull-up when there is no fault. */
    gpio.GPIO_Pin = GPIO_Pin_13;
    gpio.GPIO_Mode = GPIO_Mode_IPU;
    gpio.GPIO_Speed = GPIO_Speed_50MHz;
    GPIO_Init(GPIOB, &gpio);
}

void Vbus_Enable(void)
{
    /* EN# is active low: drive PB12 low to power the USB host port. */
    GPIO_ResetBits(GPIOB, GPIO_Pin_12);
}

void Vbus_Disable(void)
{
    GPIO_SetBits(GPIOB, GPIO_Pin_12);
}

int Vbus_Faulted(void)
{
    /* FLAG# is active low: a low level means over-current or over-temperature. */
    return GPIO_ReadInputDataBit(GPIOB, GPIO_Pin_13) == Bit_RESET;
}

/*
 * Runs from the EXTI3 vector (SLT falling edge). It services a read cycle and
 * then captures a write cycle, matching the bus timing of the cartridge
 * firmware. Keeping this in one place lets the bootloader reuse the exact
 * protocol the MSX side program expects.
 */
void MsxBus_Service(void)
{
    uint16_t address = (uint16_t)GPIOE->INDR;

    if (((uint16_t)GPIOB->INDR & MSX_RD_BIT) == 0) {
        GPIOD->CFGLR = MSX_BUS_ON;
        if (address == 0x7FFF) {
            if (msx_out.head == msx_out.tail) {
                GPIOD->OUTDR = 0x00;
            } else {
                GPIOD->OUTDR = msx_out.data[msx_out.tail];
                msx_out.tail = (uint8_t)((msx_out.tail + 1) & (MSX_OUT_SIZE - 1));
            }
        }
        if (address >= 0x4000 && address < 0x4000 + sizeof(msxterm)) {
            GPIOD->OUTDR = msxterm[address - 0x4000];
        }
        EXTI->INTFR = EXTI_Line3;
        while ((GPIOB->INDR & MSX_SLT_BIT) == 0) {
        }
        GPIOD->CFGLR = MSX_BUS_OFF;
    }

    EXTI->INTFR = EXTI_Line3;
    uint8_t write_data = (uint8_t)GPIOD->INDR;

    while ((GPIOB->INDR & MSX_SLT_BIT) == 0) {
        if (((uint16_t)GPIOB->INDR & MSX_WR_BIT) == 0) {
            if (address == 0x7FFE) {
                if (write_data != 0) {
                    /* The MSX side asked for the cartridge ROM: hand over to
                       the application firmware and reset. */
                    GPIO_WriteBit(GPIOA, GPIO_Pin_0, Bit_SET);
                    GPIO_WriteBit(GPIOA, GPIO_Pin_1, Bit_SET);
                    GPIO_WriteBit(GPIOA, GPIO_Pin_2, Bit_SET);
                    GPIO_WriteBit(GPIOA, GPIO_Pin_3, Bit_SET);
                    *MSX_CART_RAM_FLAG = 1;
                    PFIC->SCTLR |= (1u << 31);
                } else {
                    msx_terminal_requested = 1;
                }
                return;
            }
            if (address == 0x7FFD) {
                uint8_t next = (uint8_t)((msx_in.head + 1) & (MSX_IN_SIZE - 1));
                if (next != msx_in.tail) {
                    msx_in.data[msx_in.head] = write_data;
                    msx_in.head = next;
                }
            }
            return;
        }
    }
}

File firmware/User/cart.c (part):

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// GPIOB Pin     8           CS12  0x0100

// GPIOB Pin     9           M1    0x0200
// GPIOB Pin     10          MREQ  0x0400
// GPIOB Pin     11          RESH  0x0800

// GPIOC Pin     6           RESET 0x0040
// GPIOC Pin     7           WAIT  0x0080
// GPIOC Pin     8           IORQ  0x0100
// GPIOC Pin     9           BDIR  0x0200

#pragma GCC push_options
#pragma GCC optimize("Ofast")
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
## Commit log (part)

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2025-01-17 Release 1 - PCB Rev1, firmware v0.1
2025-01-17 README update
2025-01-23 firmware version v0.2
2025-01-25 Version 0.3 Stability fixes
2025-01-26 Release v0.4 NEO8 and NEO16 mappers
2025-01-26 Mapper LEDs fix version v0.4.1
2025-01-27 extention change fro mKON to KO4 and SCC to KO5
2025-02-02 Initial Structure
2025-02-02 Initial menu
2025-02-03 Main feature done.
2025-02-03 debugging
2025-02-03 Hot swappable USB
2025-02-04 autoprogram based on filenames
2025-02-04 bin update
2025-02-04 Bugfix with auto programming feature
2025-02-04 Config file for WCHISPTool_CMD
2025-02-06 Change from relative to absolute menu prints
2025-02-07 v0.6 Release Mapper change without reflashing (diag) Changes to KOMAMI WITH SCC DIS Changes to printfilename clearing buffer with 0x20 caused issues witgh longnames decoding
2025-02-09 v0.7 Release Info page after pressing1 on file menu Folders browsing support Debugging file access and long names buufer handling and file closing
2025-02-10 v0.7.1 cart.c unify and tidy up. add few DIskConnet() to make usb support more reliable.
2025-02-10 remove volatile (those variable won't change in this IRQs)
2025-02-10 v0.7.2 - another change
2025-02-10 v0.7.3 remove second USB check. In case of issues hit button 1.
2025-02-12 v0.8 - fine tuning cart.c code
2025-02-12 v0.8.1 - Literal pool optimisation
2025-02-12 v0.8.2 fix pointer
2025-02-12 v0.8.3 Konami with SCC cold boot fix
2025-02-12 Rev2 PCB
2025-02-14 v0.8.4 Additional Mirroring mapper for 16KB ROMS Menu changes added firmware version
2025-02-16 v0.9 - Toggle Short/Longnames with 9 or TxRx Pin
2025-02-16 V0.9.1 Rebooting text moved by 1 character.
2025-02-19 v0.9.2 Short name dispay fix, longname attept to make it more reliable.
2025-02-22 v0.10.0 Handle MSX Reset
2025-02-22 v0.10.0 add missing bin
2025-02-25 Release 2.0 PCB and updated firmare for this PCB
2025-03-01 v2.02 sound glitch fix
2025-03-01 v2.02 sound glitch
2025-03-03 v2.1.1 GRAPH button entry to flash screens. Tidy up of DAC configuration - no need for DMA and TIM4. This could cause issues,so bteer simplpify it. Arrow as a pointer instead of visible cursor. Look 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
2025-03-04 Terminal and boot section
2025-03-04 Rev 2.1.2 NYYRIKKI changes to cart flash firmware
2025-03-09 scc experimentation with tiimings modes adn DMA use
2025-03-09 Rev 2.1.3 SCC accuaracy fixes
2025-03-09 v2.1.3 bins
2025-03-11 Rev 2.1.4 SCC Final SCC timing fixes
2025-03-14 Enable buffer on DAC Tidy up the code GPIO Configuration Remove ShortNames jumper on PA9 and PA10
2025-03-15 Clock config change to adapt to V307 clock tree
2025-03-15 Release 2.1.5 for CH32V307
2025-03-15 v2.5.1 enable DAC buffer. Rev1 boards compatible
2025-03-17 Support for V307 in main branch
2025-03-22 Initial version 2.1
2025-03-22 Rev2 BOM
2025-03-23 Update RISKYMSXCart.csv
    Update fuse value
2025-03-30 v2.1.7 ASCII16 Mapper fix Reset fix
2025-04-02 Rev2.1 Gerbers
2025-04-20 v2.1.8 Rev2.1 PCB Design change BOM change https://github.com/arkadiuszmakarenko/RISKYMSX/issues/7 fix https://github.com/arkadiuszmakarenko/RISKYMSX/issues/6 fix FLashLED added.
2025-05-26 FATFS refactoring Initial commit
2025-05-26 schematic: add confirmed values for components with missing values
2025-05-26 pcb: update values from schematic
2025-05-26 kicad: add interactive BoM
2025-05-26 add .gitignore
2025-05-27 csv bom: fix duplicate C14
2025-05-27 csv bom: match footprint of C7 in BoM to that of the PCB
2025-05-27 csv bom: fix fuse name
2025-05-27 csv bom: add missing R10
2025-05-27 csv bom: rename leds with board names
2025-05-27 Specify confirmed values in BoM, schematic and PCB, fix minor csv bom issues, add .gitignore (#10)
    * schematic: add confirmed values for components with missing values
    * pcb: update values from schematic
    * kicad: add interactive BoM
    * add .gitignore
    * csv bom: fix duplicate C14
    * csv bom: match footprint of C7 in BoM to that of the PCB
2025-05-28 Improved diskio.c functions. Reduce need to delay_ms
2025-05-28 bin added
2025-05-28 Main functionality completed
2025-05-28 add bin
2025-05-30 v3.1.1
2025-05-30 bin and tidy up
2025-05-30 v3.1.2 flush button to prevent sticky keyboard presses
2025-05-31 Programming speed improvements
2025-05-31 readme: first round of documentation improvements
2025-06-01 readme: first round of documentation improvements (#12)
2025-06-02 readme: second round of documentation enhancements
    Enhance information for building and flashing the cartridge using
    the MounRiverStudio IDE.
    Add back supported machines removed by mistake.
2025-06-03 readme: second round of documentation enhancements (#13)
    Enhance information for building and flashing the cartridge using
    the MounRiverStudio IDE.
    Add back supported machines removed by mistake.
2025-06-03 readme: third round of documentation improvements
    Add instructions for WCHISPTool_CMD.
    Add cartridge operation instructions.
    Minor fixes.
2025-06-03 readme: third round of documentation improvements (#14)
    Add instructions for WCHISPTool_CMD.
    Add cartridge operation instructions.
    Minor fixes.
2025-06-04 v.3.2.1 - fix fast flashing issues
2025-06-16 readme: add section for enclosures
2025-06-16 readme: add section for enclosures (#17)
2025-07-10 v.3.2.2 Minor tidy up. Removed onchip memory split
2025-08-23 USB init fiix
2025-09-15 consolidate filesystem mount
2025-09-15 consolidate auto programming
2025-09-15 consolidate file array size constant
2025-09-15 improve file menu navigation
2025-09-21 Small code cleanups and file navigation enhancements (#22)
    * consolidate auto programming
    * consolidate filesystem mount
    * consolidate file array size constant
    * improve file menu navigation
    ---------
2025-09-21 version update
2025-09-28 Add file size as hint to mapper flash screen
2025-09-28 Fit filename and size in one line
2025-09-28 Align filename in flash progress screen
2025-10-19 Add file size as hint to mapper flash screen and minor visual fixes (#23)
    * Add file size as hint to mapper flash screen
    * Fit filename and size in one line
    * Align filename in flash progress screen
    ---------
2025-10-19 new binary
2025-10-19 FATFS upgrade to 0.16
2025-10-19 usb drive support improvement
2025-10-19 Small firmware size improvements
2025-10-19 reduce firmware size by configuring fatfs added warning to not hold msx keys during flashing
2025-10-19 some more size optimisations
2025-10-19 version change
2025-10-23 inital version
2025-10-23 updated flash
2025-10-23 size optimisations
2025-10-26 intial makefile with flash
2025-10-28 Buiulding Makefile and additional prep for autoupgrade flash process
2025-10-29 Bootloader firmware added
2026-02-27 fix htmlpreview link
